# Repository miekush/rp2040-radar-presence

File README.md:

# RP2040 Radar Presence Sensor
RP2040/LD2410 based Radar Presence sensor

# Documentation

I created a short description for this project on Hackaday.io! See the project page [HERE](https://hackaday.io/project/193141-radar-halloween-candy-basket-light)!

# License

MKE supports the open source hardware community by sharing hardware design files freely on GitHub!

Please support MKE by purchasing products on [Tindie](https://www.tindie.com/stores/mkengineering/)!

Designed by Mike Kushnerik (miekush)

Licensed under [Creative Commons Attribution-ShareAlike CC BY-SA 4.0](http://creativecommons.org/licenses/by-sa/4.0/)

All text above must be included in any redistribution!

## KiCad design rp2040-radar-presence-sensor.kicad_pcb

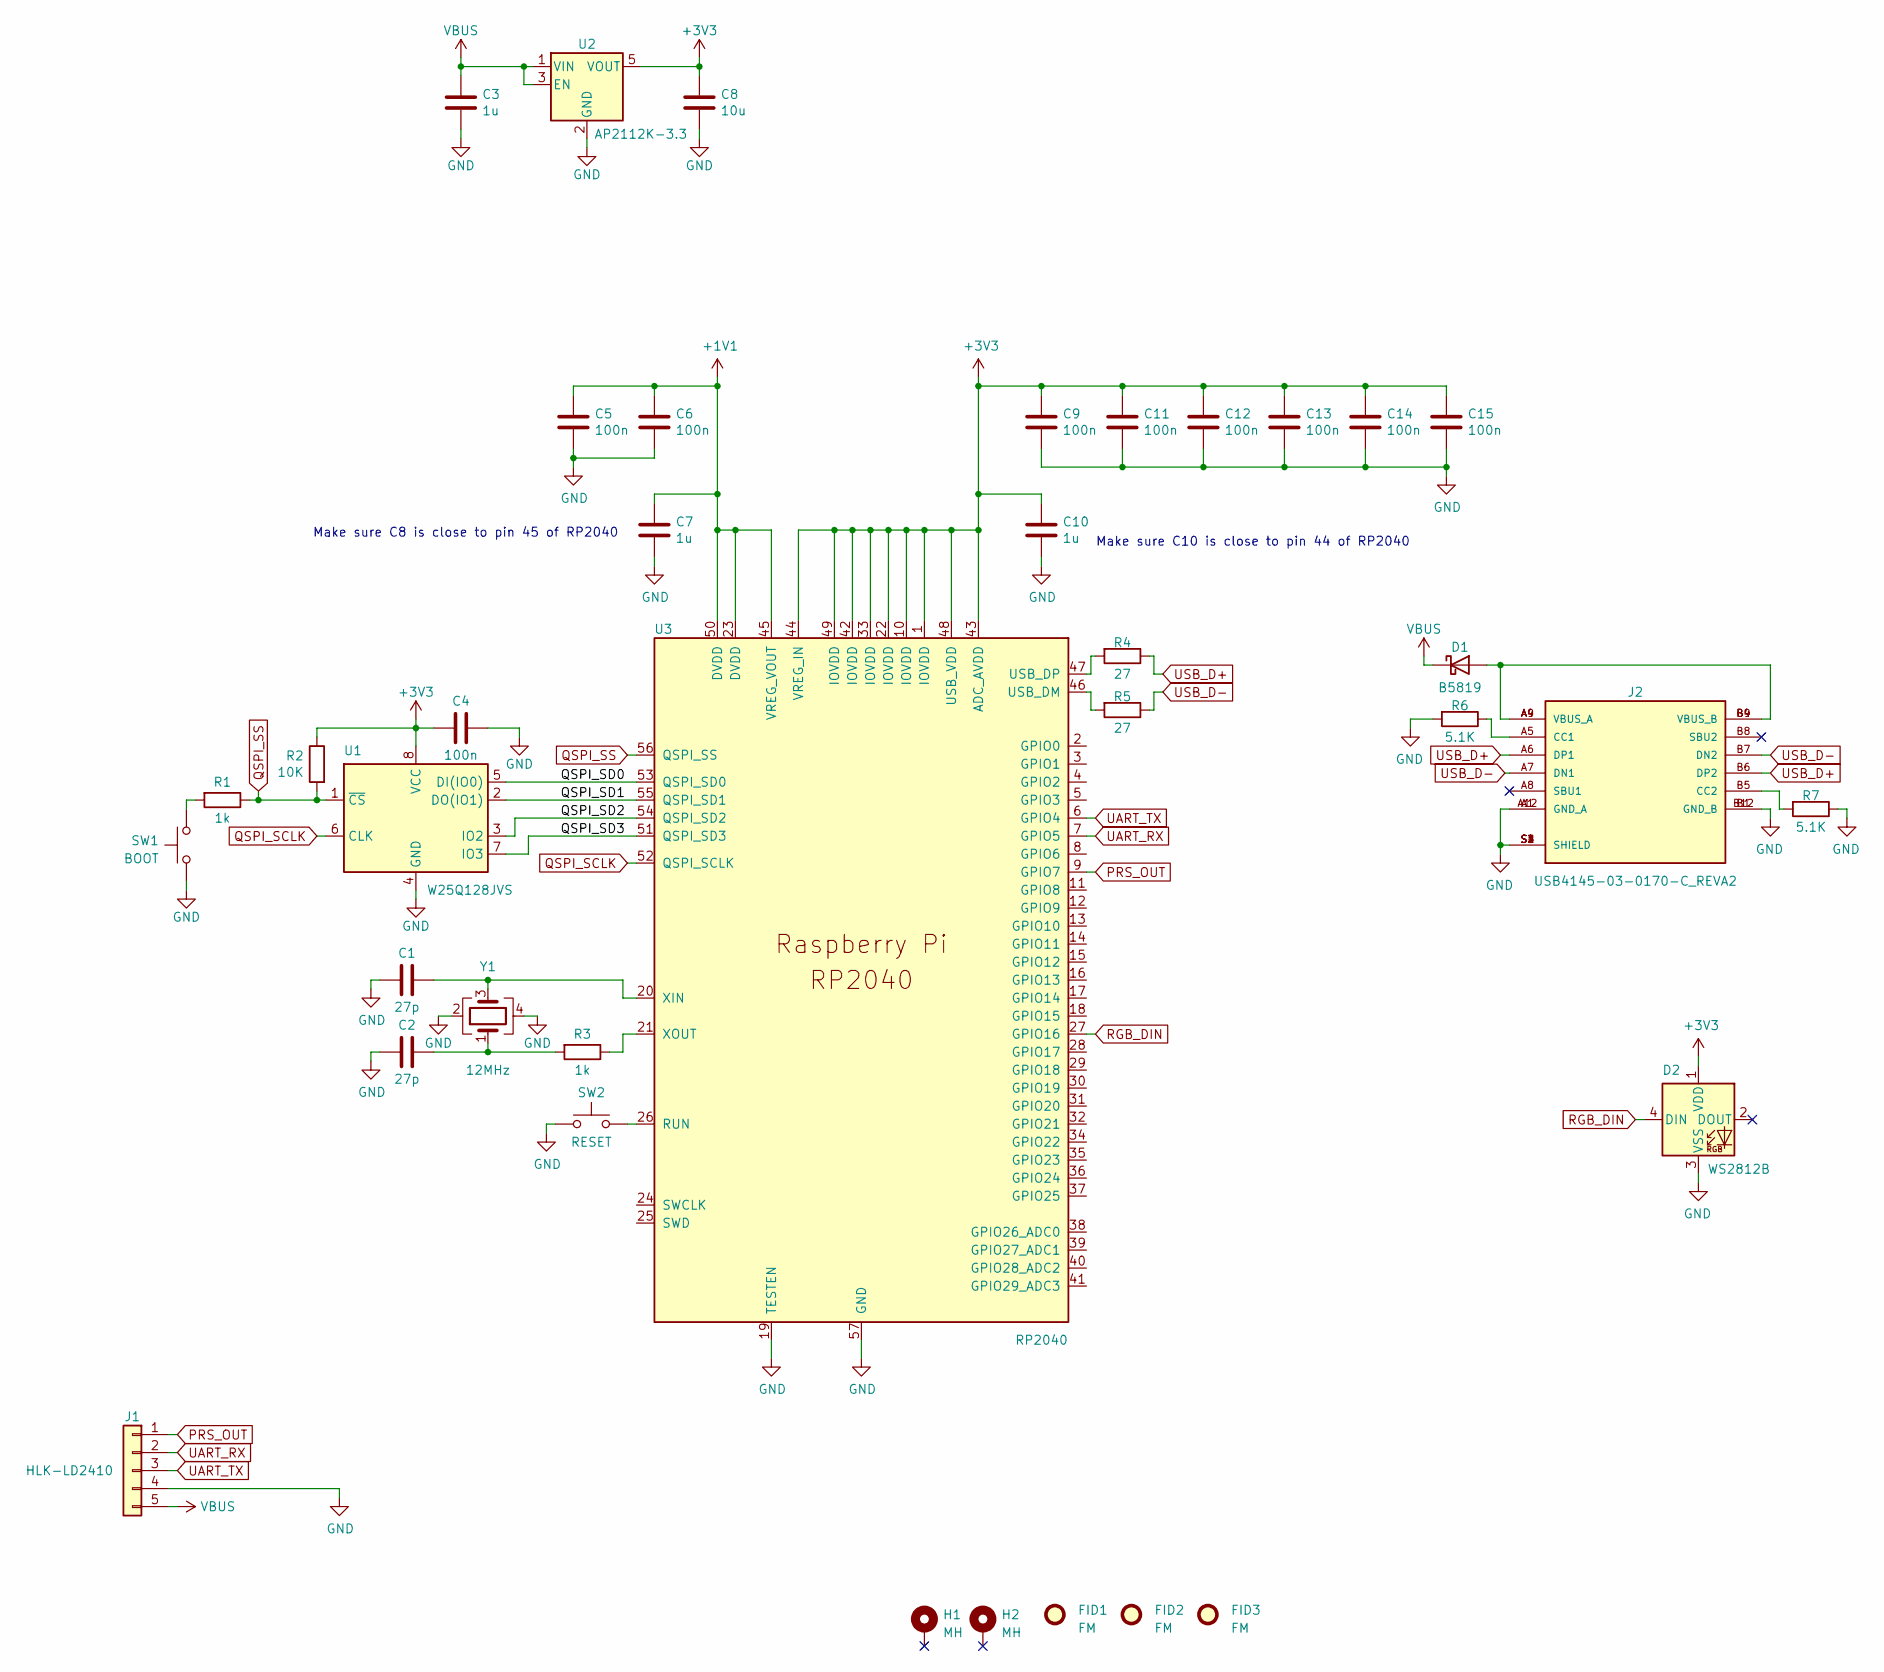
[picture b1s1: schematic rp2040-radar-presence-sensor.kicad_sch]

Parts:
C1, C2: 27p; C_0603_1608Metric
C3, C7, C10: 1u; C_0603_1608Metric
C4, C5, C6, C9, C11, C12, C13, C14, C15: 100n; C_0603_1608Metric
C8: 10u; C_0805_2012Metric
D1: B5819; D_SOD-323
D2: WS2812B; LED_WS2812B_PLCC4_5.0x5.0mm_P3.2mm
FID1, FID2, FID3: FM; Fiducial_1mm_Mask2mm
H1, H2: MH; MountingHole_2.2mm_M2_Pad
J1: HLK-LD2410; PinHeader_1x05_P1.27mm_Vertical
J2: USB4145-03-0170-C_REVA2; GCT_USB4145-03-0170-C_REVA2; PARTREV A2
R1, R3: 1k; R_0603_1608Metric
R2: 10K; R_0603_1608Metric
R4, R5: 27; R_0603_1608Metric
R6, R7: 5.1K; R_0603_1608Metric
SW1: BOOT; SW_Push_1P1T_NO_CK_KMR2
SW2: RESET; SW_Push_1P1T_NO_CK_KMR2
U1: W25Q128JVS; SOIC-8_5.23x5.23mm_P1.27mm
U2: AP2112K-3.3; SOT-23-5
U3: RP2040; RP2040-QFN-56
Y1: 12MHz; Crystal_SMD_Abracon_ABM8G-4Pin_3.2x2.5mm

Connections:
+1V1: C5.1, C6.1, C7.1, U3.23 (DVDD), U3.45 (VREG_VOUT), U3.50 (DVDD)
+3V3: C4.1, C8.1, C9.1, C10.1, C11.1, C12.1, C13.1, C14.1, C15.1, D2.1 (VDD), R2.1, U1.8 (VCC), U2.5 (VOUT), U3.1 (IOVDD), U3.10 (IOVDD), U3.22 (IOVDD), U3.33 (IOVDD), U3.42 (IOVDD), U3.43 (ADC_AVDD), U3.44 (VREG_IN), U3.48 (USB_VDD), U3.49 (IOVDD)
/QSPI_SD0: U1.5 (DI(IO0)), U3.53 (QSPI_SD0)
/QSPI_SD1: U1.2 (DO(IO1)), U3.55 (QSPI_SD1)
/QSPI_SD2: U1.3 (IO2), U3.54 (QSPI_SD2)
/QSPI_SD3: U1.7 (IO3), U3.51 (QSPI_SD3)
GND: C1.2, C2.2, C3.2, C4.2, C5.2, C6.2, C7.2, C8.2, C9.2, C10.2, C11.2, C12.2, C13.2, C14.2, C15.2, D2.3 (VSS), J1.4, J2.A1 (GND_A), J2.A12 (GND_A), J2.B1 (GND_B), J2.B12 (GND_B), J2.S1 (SHIELD), J2.S2 (SHIELD), J2.S3 (SHIELD), J2.S4 (SHIELD), R6.2, R7.1, SW1.1, SW2.1, U1.4 (GND), U2.2 (GND), U3.19 (TESTEN), U3.57 (GND), Y1.2, Y1.4
unnamed: C2.1, R3.2, Y1.1
unnamed: D1.2 (A), J2.A4 (VBUS_A), J2.A9 (VBUS_A), J2.B4 (VBUS_B), J2.B9 (VBUS_B)
unnamed: J2.A5 (CC1), R6.1
unnamed: J2.B5 (CC2), R7.2
unnamed: R1.2, SW1.2
unnamed: SW2.2, U3.26 (RUN)
unnamed: R5.2, U3.46 (USB_DM)
unnamed: R4.2, U3.47 (USB_DP)
unnamed: C1.1, U3.20 (XIN), Y1.3
unnamed: R3.1, U3.21 (XOUT)
PRS_OUT: J1.1, U3.9 (GPIO7)
QSPI_SCLK: U1.6 (CLK), U3.52 (QSPI_SCLK)
QSPI_SS: R1.1, R2.2, U1.1 (~CS), U3.56 (QSPI_SS)
RGB_DIN: D2.4 (DIN), U3.27 (GPIO16)
UART_RX: J1.2, U3.7 (GPIO5)
UART_TX: J1.3, U3.6 (GPIO4)
USB_D+: J2.A6 (DP1), J2.B6 (DP2), R4.1
USB_D-: J2.A7 (DN1), J2.B7 (DN2), R5.1
VBUS: C3.1, D1.1 (K), J1.5, U2.1 (VIN), U2.3 (EN)

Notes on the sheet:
Make sure C8 is close to pin 45 of RP2040
Make sure C10 is close to pin 44 of RP2040

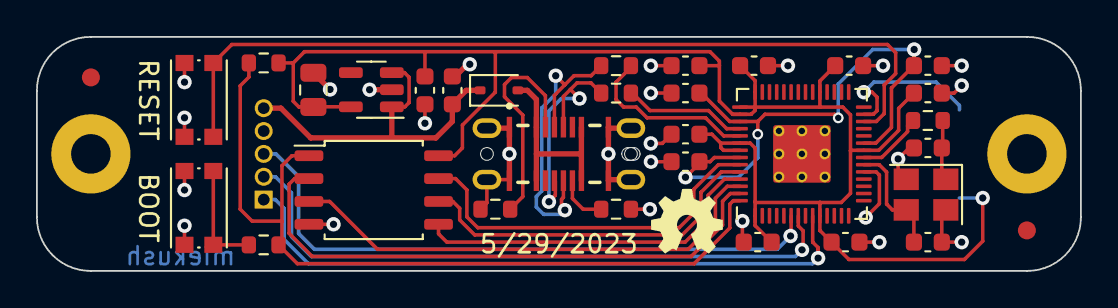
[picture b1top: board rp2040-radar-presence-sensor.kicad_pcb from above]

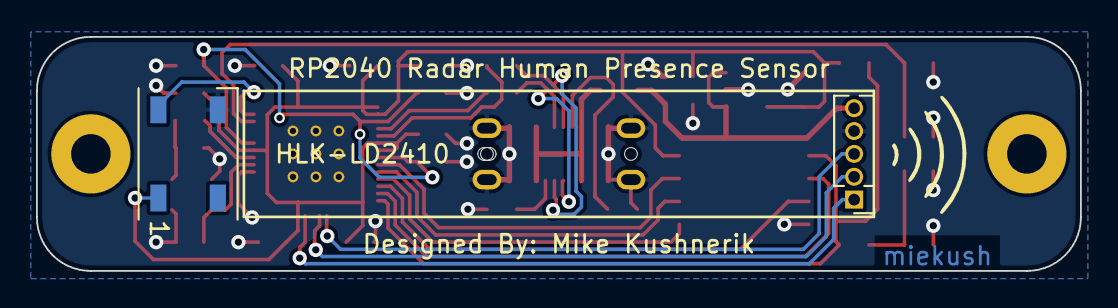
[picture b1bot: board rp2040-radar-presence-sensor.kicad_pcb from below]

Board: 2 copper layers, 58.0 x 13.0 mm, 36 parts (2 on the bottom side), 26 nets.

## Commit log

2023-10-12 Initial upload
